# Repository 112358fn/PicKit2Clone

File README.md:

# PicKit2Clone
PicKit2 Clone 5V/3.3V by Suky

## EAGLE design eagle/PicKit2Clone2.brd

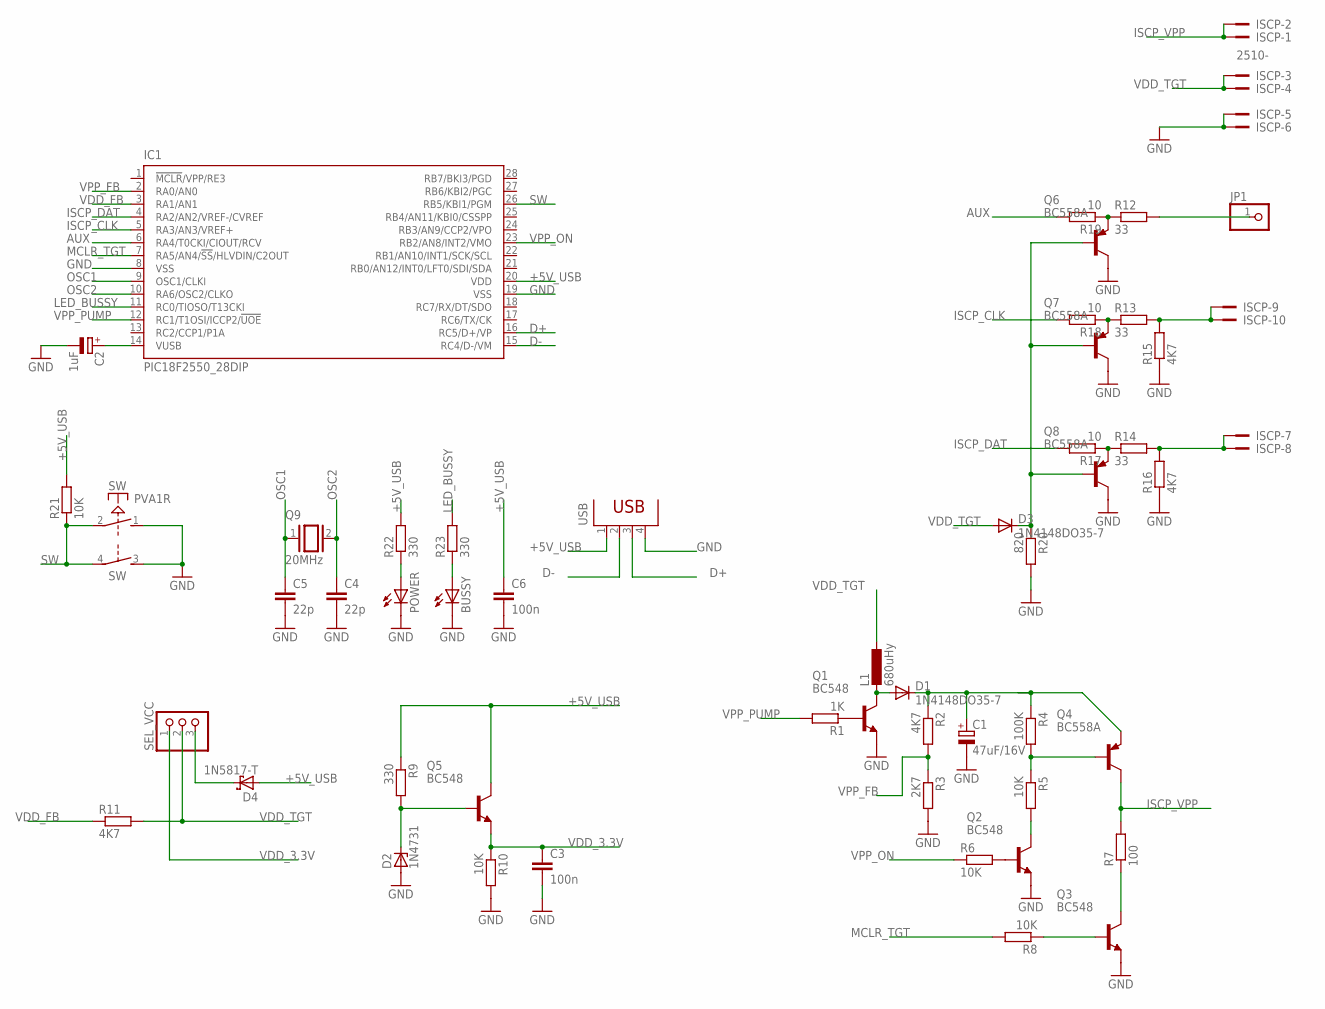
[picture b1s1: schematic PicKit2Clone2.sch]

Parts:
BUSSY: LED5MM
C1: 47uF/16V; E1,8-4
C2: 1uF; E1,8-4
C3: 100n; C025-025X050
C4, C5: 22p; C025-024X044
C6: 100n; C025-024X044
D1, D3: 1N4148DO35-7; DO35-7
D2: 1N4731; DO41Z10
D4: 1N5817-T; DO41-7.6
IC1: PIC18F2550_28DIP; DIL28-3
ISCP: 2510-; PAK100/2500-10
JP1: PINHD-1X1; 1X01
L1: 680uHy; 0204/5
POWER: LED5MM
Q1, Q2, Q3, Q5: BC548; TO92-EBC
Q4, Q6, Q7, Q8: BC558A; TO92-EBC
Q9: 20MHz; QS
R1: 1K; 0204/5
R2, R11, R15: 4K7; 0204/5
R3: 2K7; 0204/5
R4: 100K; 0204/5
R5, R10, R21: 10K; 0204/5
R6, R8: 10K; 0204/7
R7: 100; 0204/5
R9: 330; 0204/7
R12, R13: 33; 0204/5
R14: 33; 0204/7
R16: 4K7; 0204/7
R17, R18, R19: 10; 0204/5
R20: 820; 0204/5
R22, R23: 330; 0204/5
SEL_VCC: PINHD-1X3; 1X03
SW: PVA1R
USB: PN61729

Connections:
+5V_USB: C6.1, D4.A, IC1.20 (VDD), Q5.C, R9.1, R21.2, R22.2, USB.1
AUX: IC1.6 (RA4/T0CKI/CIOUT/RCV), R19.2
D+: IC1.16 (RC5/D+/VP), USB.3
D-: IC1.15 (RC4/D-/VM), USB.2
GND: BUSSY.K (C), C1.-, C2.-, C3.2, C4.2, C5.2, C6.2, D2.A, IC1.8 (VSS), IC1.19 (VSS), ISCP.5, ISCP.6, POWER.K (C), Q1.E, Q2.E, Q3.E, Q6.C, Q7.C, Q8.C, R3.2, R10.2, R15.1, R16.1, R20.2, SW.1 (S), SW.3 (S), USB.4
ISCP_CLK: IC1.5 (RA3/AN3/VREF+), R18.2
ISCP_DAT: IC1.4 (RA2/AN2/VREF-/CVREF), R17.2
ISCP_VPP: ISCP.1, ISCP.2, Q4.C, R7.2
LED_BUSSY: IC1.11 (RC0/TIOSO/T13CKI), R23.2
MCLR_TGT: IC1.7 (RA5/AN4/!SS!/HLVDIN/C2OUT), R8.2
unnamed: D1.A, L1.2, Q1.C
unnamed: Q1.B, R1.1
unnamed: C1.+, D1.C, Q4.E, R2.1, R4.1
unnamed: Q4.B, R4.2, R5.1
unnamed: D2.C, Q5.B, R9.2
unnamed: Q2.C, R5.2
unnamed: Q2.B, R6.2
unnamed: Q3.B, R8.1
unnamed: Q3.C, R7.1
unnamed: C2.+, IC1.14 (VUSB)
unnamed: D4.C, SEL_VCC.3
unnamed: Q6.E, R12.1, R19.1
unnamed: Q7.E, R13.1, R18.1
unnamed: Q8.E, R14.1, R17.1
unnamed: ISCP.9, ISCP.10, R13.2, R15.2
unnamed: ISCP.7, ISCP.8, R14.2, R16.2
unnamed: D3.C, Q6.B, Q7.B, Q8.B, R20.1
unnamed: JP1.1, R12.2
unnamed: BUSSY.A, R23.1
unnamed: POWER.A, R22.1
OSC1: C5.1, IC1.9 (OSC1/CLKI), Q9.1
OSC2: C4.1, IC1.10 (RA6/OSC2/CLKO), Q9.2
SW: IC1.26 (RB5/KBI1/PGM), R21.1, SW.2, SW.4
VDD_3.3V: C3.1, Q5.E, R10.1, SEL_VCC.1
VDD_FB: IC1.3 (RA1/AN1), R11.1
VDD_TGT: D3.A, ISCP.3, ISCP.4, L1.1, R11.2, SEL_VCC.2
VPP_FB: IC1.2 (RA0/AN0), R2.2, R3.1
VPP_ON: IC1.23 (RB2/AN8/INT2/VMO), R6.1
VPP_PUMP: IC1.12 (RC1/T1OSI/ICCP2/!UOE), R1.2

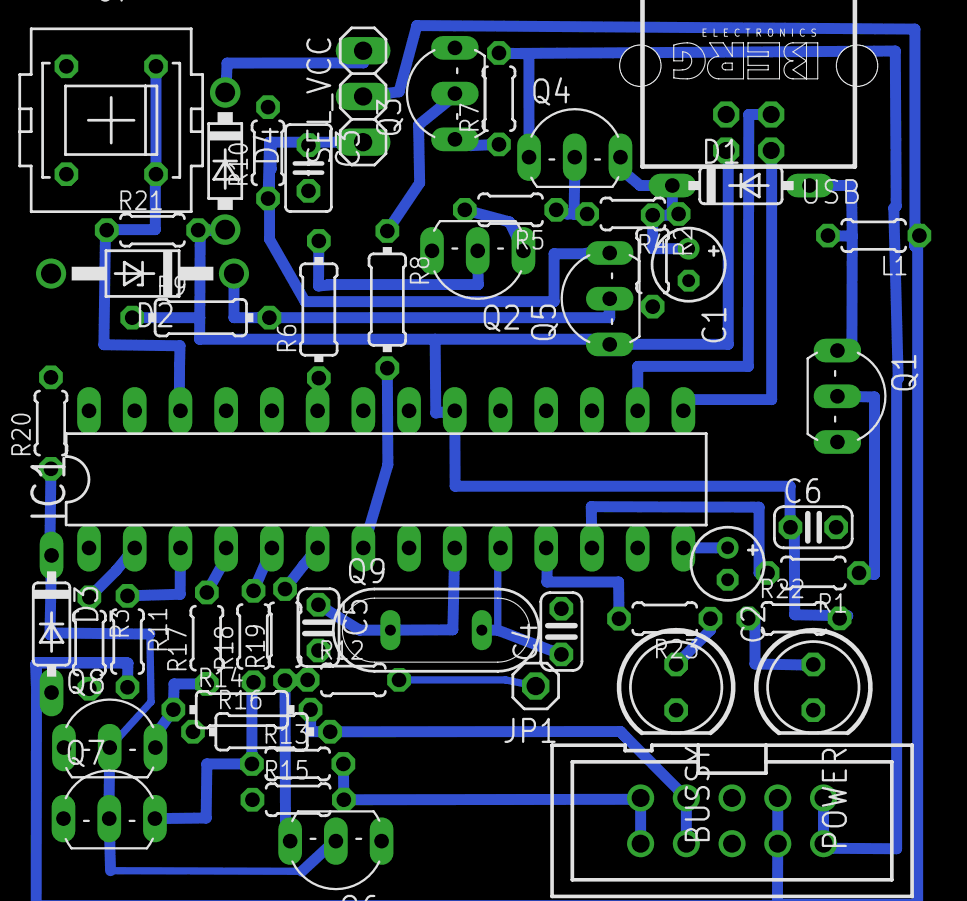
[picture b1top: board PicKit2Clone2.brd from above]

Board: 2 copper layers, 51 parts (0 on the bottom side), 39 nets.

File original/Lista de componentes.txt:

Capacitores:
C1  47uF 16V

C2  1uF 

C3  100nF

C4  22pF

C5  22pF

C6  100nF


Diodos:
D1  1N4148

D2  Zener 4V3 (1N4731)

D3  1N4148

D4  1N5817 (1N5818, 1N5819, Diodo schottky)


PIC:
IC1 PIC18F2550


Bobina:
L1  680uH (desde 470uHy a 1mHy)


LED BUSY Rojo
LED POWER Verde

Transistores:
Q1  BC548

Q2  BC548

Q3  BC548

Q4  BC558A

Q5  BC548

Q6  BC558A

Q7  BC558A

Q8  BC558A


Oscilador:
Q9  20MHz


Resistencias:
R1     1K

R10   10K

R11   4k7

R12    33

R13    33

R14    33

R15   4K7

R16   4K7

R17    10

R18    10

R19    10

R2    4K7

R20    1k
 (reemplaza la de 820)
R21   10k

R22   330

R23   330

R3    2K7

R4   100K

R5    10K

R6    10K

R7    100

R8    10K

R9    330


Zocalo 28 pin
Cable usb
Cables para puentear
Boton pulsador
Tira pines hembra y macho

Estaño
Cloruro Ferrico
Plaqueta de cobre de 10*5 cm
Mecha 1mm
Acetona
Alcohol isopropilico

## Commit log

2015-11-07 Agregados archivos de eagle
2015-11-07 Esquematico terminado
2015-11-07 Agregados archivos originales
2015-11-08 PCB a revisar
2015-11-09 Single layer Done
2015-11-10 Placa de 5x5. Doble capa no es util
2015-11-10 mejora de 5x5
2015-11-19 cambios menores
